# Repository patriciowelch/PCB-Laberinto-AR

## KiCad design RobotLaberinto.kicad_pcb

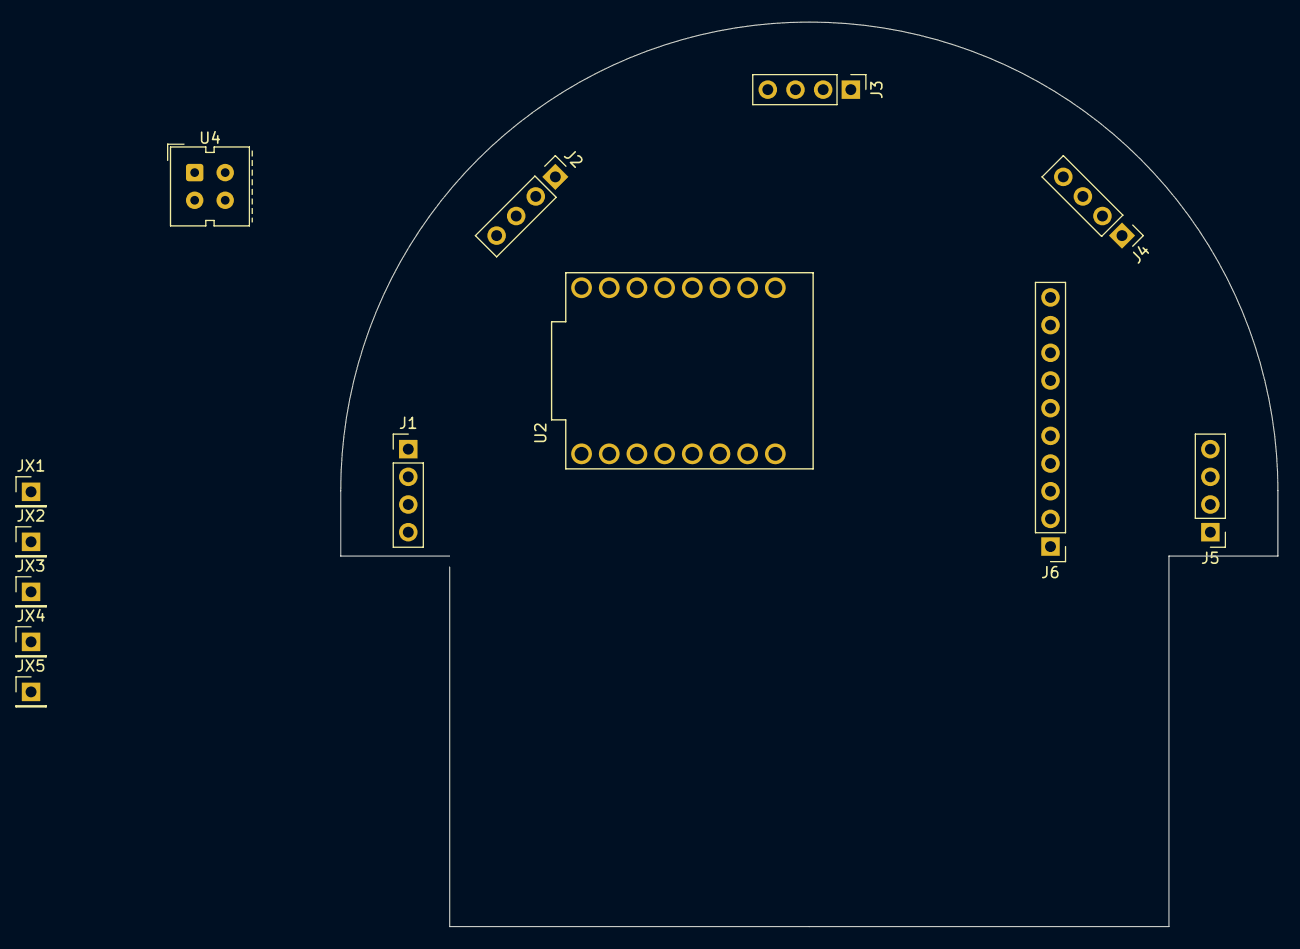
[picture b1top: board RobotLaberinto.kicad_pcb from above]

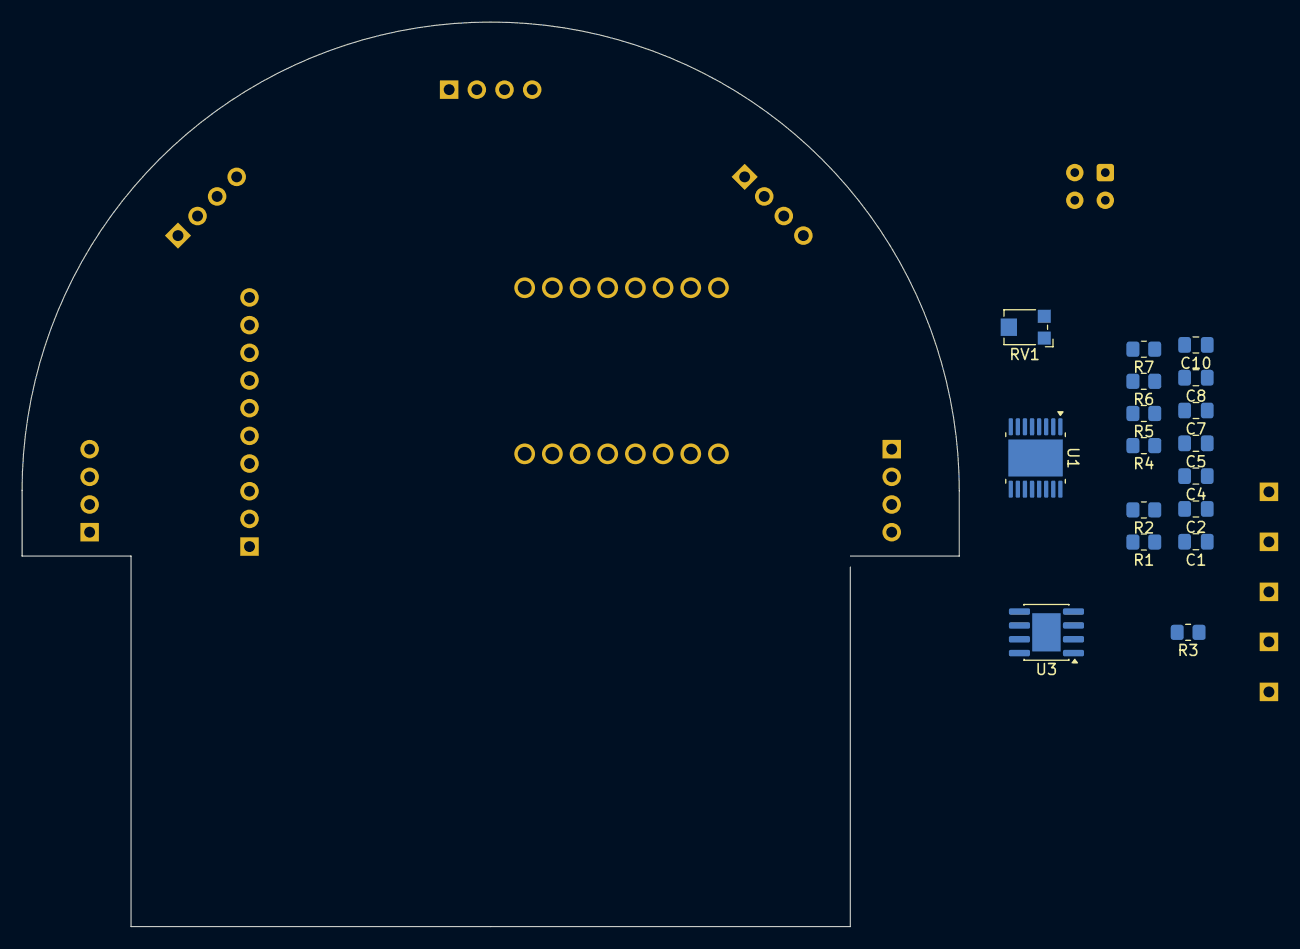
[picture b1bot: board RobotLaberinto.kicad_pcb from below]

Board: 2 copper layers, 86.0 x 83.0 mm, 30 parts (17 on the bottom side), 20 nets, no tracks yet.

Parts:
C1, C2: 10u; C_0805_2012Metric_Pad1.18x1.45mm_HandSolder
C4: 100n; C_0805_2012Metric_Pad1.18x1.45mm_HandSolder
C5: 3.9n; C_0805_2012Metric_Pad1.18x1.45mm_HandSolder
C7: 2.2u; C_0805_2012Metric_Pad1.18x1.45mm_HandSolder
C8, C10: 10n; C_0805_2012Metric_Pad1.18x1.45mm_HandSolder
J1, J2, J3, J4, J5: VL53LDK; PinHeader_1x04_P2.54mm_Vertical
J6: BNO08; PinHeader_1x10_P2.54mm_Vertical
JX1, JX2, JX3, JX4, JX5: VL53LDK; PinHeader_1x01_P2.54mm_Vertical
R1, R2, R5: 10k; R_0805_2012Metric_Pad1.20x1.40mm_HandSolder
R3: 100k; R_0805_2012Metric_Pad1.20x1.40mm_HandSolder
R4: 6k8; R_0805_2012Metric_Pad1.20x1.40mm_HandSolder
R6, R7: 100; R_0805_2012Metric_Pad1.20x1.40mm_HandSolder
RV1: R_Potentiometer_Trim; Potentiometer_Bourns_TC33X_Vertical
U1: DRV8833PWP; HTSSOP-16-1EP_4.4x5mm_P0.65mm_EP3.4x5mm_Mask2.78x3.37mm
U2: ESP32-C3_SUPERMINI_TH; MODULE_ESP32-C3_SUPERMINI
U3: MP2307; SOIC-8-1EP_3.9x4.9mm_P1.27mm_EP2.62x3.51mm
U4: CNY70; Vishay_CNY70

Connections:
3V3: J1.1, J2.1, J3.1, J4.1, J5.1, J6.1, JX1.1 (Pin_1_1), R6.2, RV1.2, U2.3.3 (3V3), U4.3 (C)
B+: C8.1, R3.1, U1.12 (VM), U3.2 (IN)
CNY: R7.2, U4.4 (E)
GND: C1.2, C2.2, C4.1, C7.1, J1.2, J2.2, J3.2, J4.2, J5.2, J6.2, R4.2, R5.2, R7.1, U1.3 (AISEN), U1.6 (BISEN), U1.13 (GND), U1.17 (GND), U2.G (GND), U3.4 (GND), U4.2 (K)
unnamed: C5.1, R4.1
unnamed: C1.1, JX3.1 (Pin_1_1), R1.2
unnamed: C2.1, JX5.1 (Pin_1_1), R2.2
unnamed: C8.2, U1.11 (VCP)
unnamed: C7.2, U1.1 (~SLEEP), U1.14 (VINT)
unnamed: C10.2, U3.1 (BS)
unnamed: C5.2, U3.6 (COMP)
unnamed: R3.2, U3.7 (EN)
unnamed: R5.1, RV1.3, U3.5 (FB)
unnamed: C4.2, U3.8 (SS)
unnamed: C10.1, U3.3 (SW)
unnamed: R6.1, U4.1 (A)
SCL: J1.3, J2.3, J3.3, J4.3, J5.3, J6.3, U2.6 (GPIO6)
SDA: J1.4, J2.4, J3.4, J4.4, J5.4, J6.4, U2.5 (GPIO5)
XSHUT1: JX2.1 (Pin_1_1), R1.1
XSHUT2: JX4.1 (Pin_1_1), R2.1
